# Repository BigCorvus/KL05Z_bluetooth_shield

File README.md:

# KL05Z_bluetooth_shield
A shield to plug on top of the KL05Z breakout board. Uses the HC05 bluetooth module. This is also used in my biosignal amplifier.

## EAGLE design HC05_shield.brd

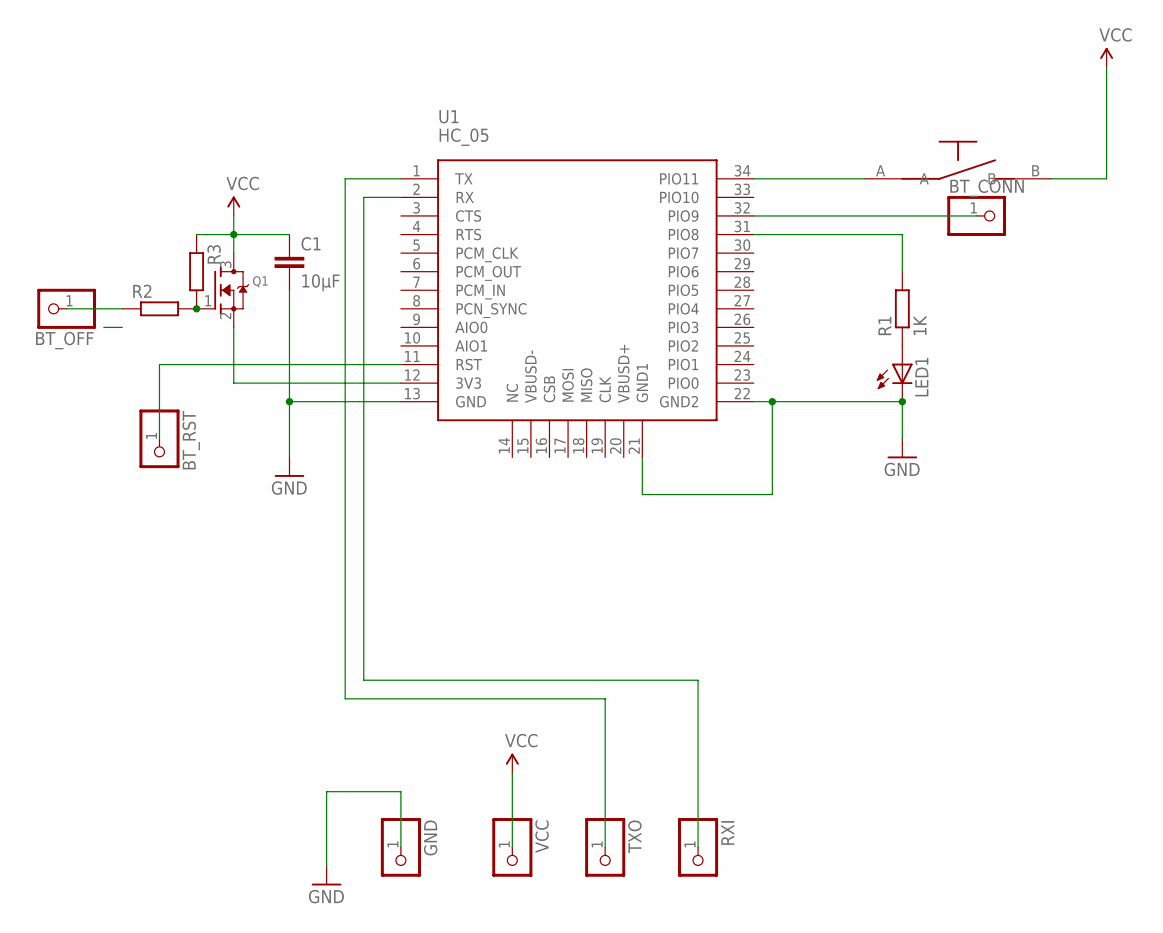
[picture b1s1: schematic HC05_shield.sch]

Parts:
BT_CONN: PINHD-1X1; 1X01
BT_OFF: PINHD-1X1; 1X01
BT_RST: PINHD-1X1; 1X01
C1: 10µF; C0805
GND: PINHD-1X1; 1X01
LED1: LEDCHIP-LED0805; CHIP-LED0805
Q1: MOSFET-NREFLOW; SOT23
R1: 1K; R0805
R2, R3: R-EU_R0603; R0603
RXI: PINHD-1X1; 1X01
TXO: PINHD-1X1; 1X01
U1: HC_05; BLUETOOTH_SMD
U$2: SWITCH2PIN
VCC: PINHD-1X1; 1X01

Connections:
BT_RST: BT_RST.1, U1.11 (RST)
GND: C1.2, GND.1, LED1.C, U1.13 (GND), U1.21 (GND1), U1.22 (GND2)
unnamed: U1.34 (PIO11), U$2.A
unnamed: Q1.1 (G), R2.2, R3.2
unnamed: LED1.A, R1.1
unnamed: TXO.1, U1.1 (TX)
unnamed: RXI.1, U1.2 (RX)
unnamed: BT_CONN.1, U1.32 (PIO9)
unnamed: R1.2, U1.31 (PIO8)
unnamed: Q1.2 (S), U1.12 (3V3)
unnamed: BT_OFF.1, R2.1
VCC: C1.1, Q1.3 (D), R3.1, U$2.B, VCC.1

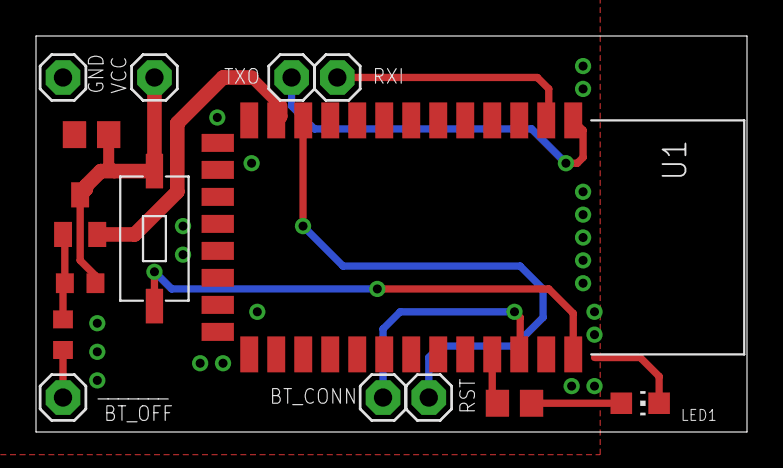
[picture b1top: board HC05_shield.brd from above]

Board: 2 copper layers, 39.5 x 22.0 mm, 15 parts (0 on the bottom side), 12 nets.

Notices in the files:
parts and their libraries:
SparkFun-Aesthetics: Licensing: Creative Commons ShareAlike 4.0 International - https://creativecommons.org/licenses/by-sa/4.0
